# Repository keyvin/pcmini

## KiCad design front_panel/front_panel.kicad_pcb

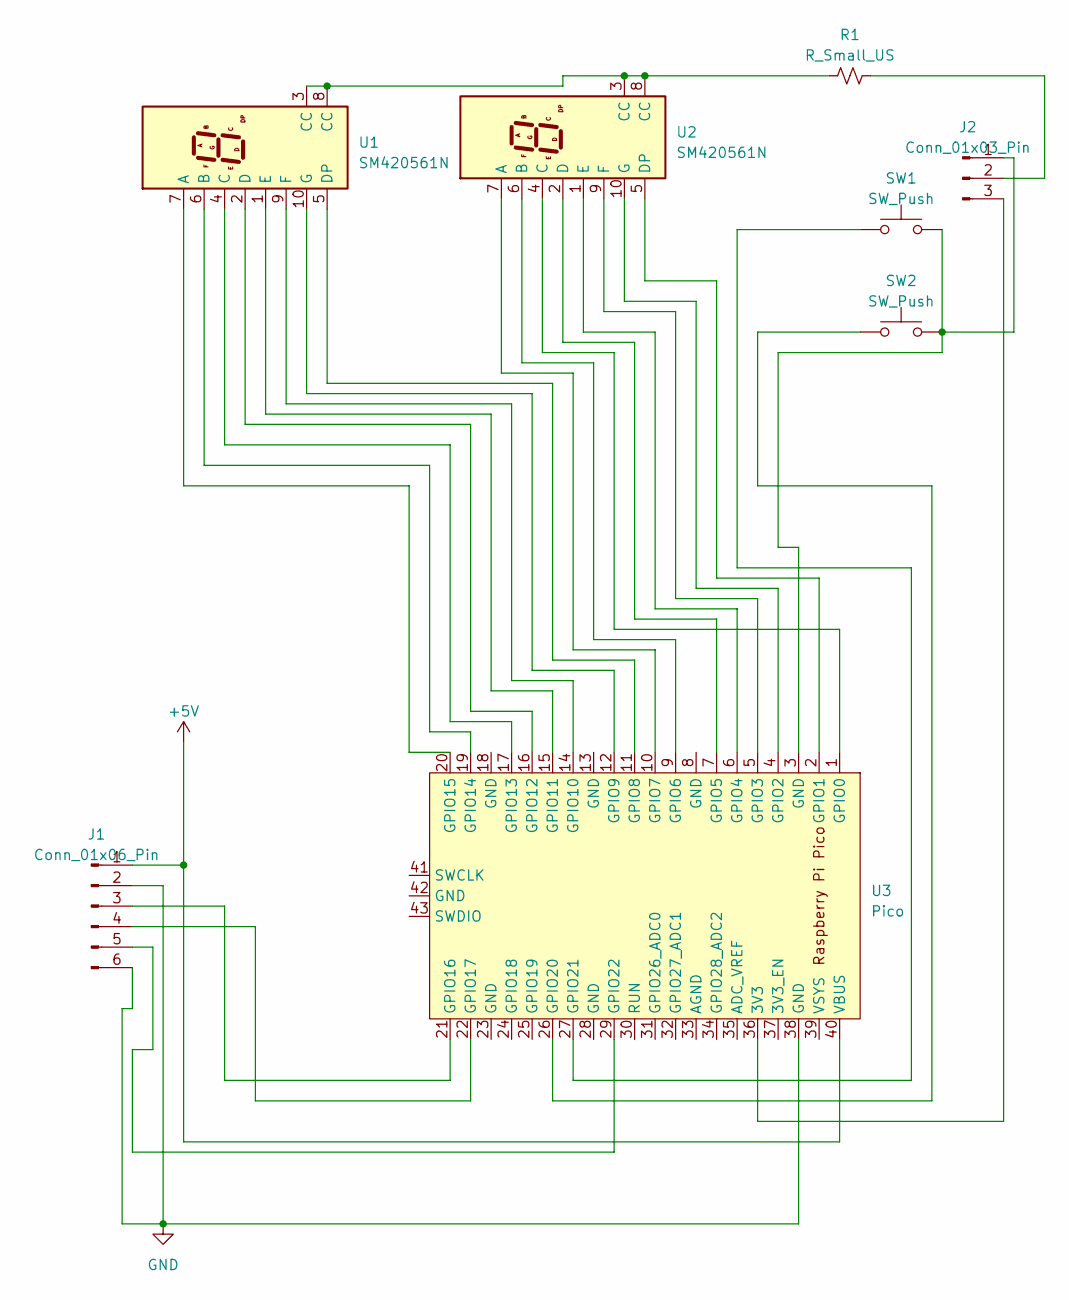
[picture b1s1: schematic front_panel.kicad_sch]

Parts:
J1: Conn_01x06_Pin; PinHeader_1x06_P2.54mm_Vertical
J2: Conn_01x03_Pin; PinHeader_1x03_P2.54mm_Vertical
R1: R_Small_US; R_Axial_DIN0207_L6.3mm_D2.5mm_P7.62mm_Horizontal
SW1, SW2: SW_Push; SW_PUSH-12mm
U1, U2: SM420561N; 7SegmentLED_LTS6760_LTS6780
U3: Pico; RPi_Pico_SMD_TH

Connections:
+5V: J1.1, U3.40 (VBUS)
GND: J1.2, J1.6, U3.38 (GND)
unnamed: J1.3, U3.21 (GPIO16)
unnamed: J1.4, U3.22 (GPIO17)
unnamed: J1.5, U3.29 (GPIO22)
unnamed: J2.1, SW1.2, SW2.2, U3.3 (GND)
unnamed: J2.2, R1.2
unnamed: J2.3, U3.36 (3V3)
unnamed: R1.1, U1.3 (CC), U1.8 (CC), U2.3 (CC), U2.8 (CC)
unnamed: U1.7 (A), U3.20 (GPIO15)
unnamed: U1.6 (B), U3.19 (GPIO14)
unnamed: U1.4 (C), U3.17 (GPIO13)
unnamed: U1.2 (D), U3.16 (GPIO12)
unnamed: U1.5 (DP), U3.11 (GPIO8)
unnamed: U1.1 (E), U3.15 (GPIO11)
unnamed: U1.9 (F), U3.14 (GPIO10)
unnamed: U1.10 (G), U3.12 (GPIO9)
unnamed: U2.7 (A), U3.10 (GPIO7)
unnamed: U2.6 (B), U3.9 (GPIO6)
unnamed: U2.4 (C), U3.1 (GPIO0)
unnamed: U2.2 (D), U3.7 (GPIO5)
unnamed: U2.5 (DP), U3.2 (GPIO1)
unnamed: U2.1 (E), U3.6 (GPIO4)
unnamed: U2.9 (F), U3.5 (GPIO3)
unnamed: U2.10 (G), U3.4 (GPIO2)
unnamed: SW2.1, U3.26 (GPIO20)
unnamed: SW1.1, U3.27 (GPIO21)

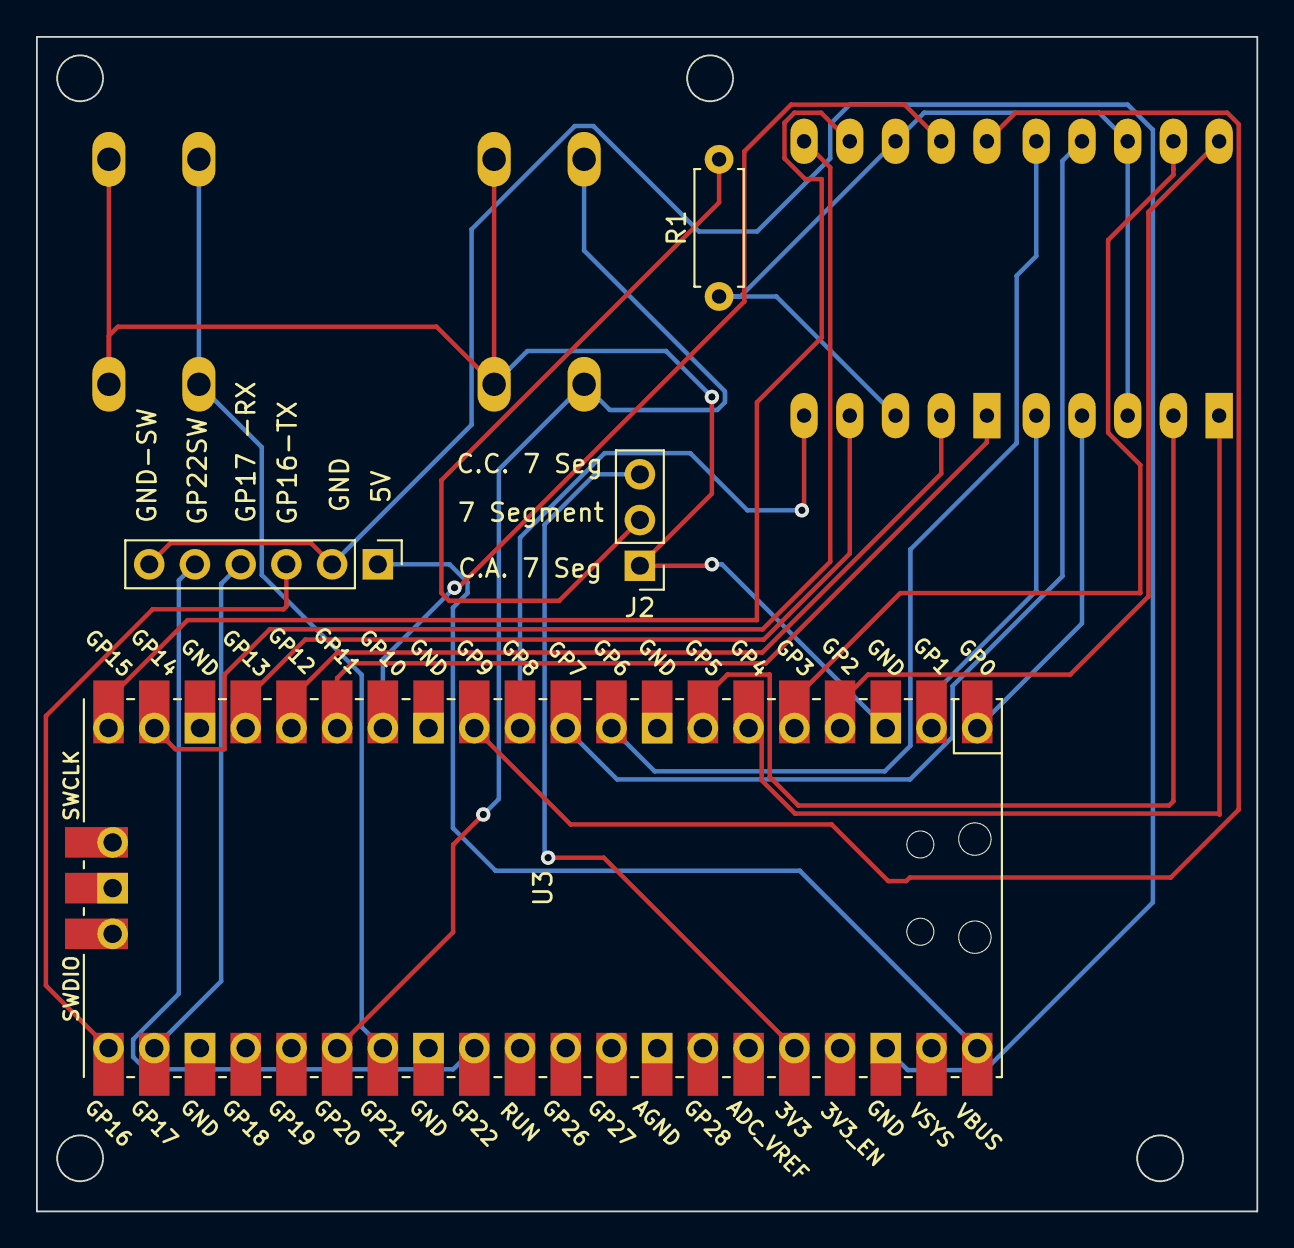
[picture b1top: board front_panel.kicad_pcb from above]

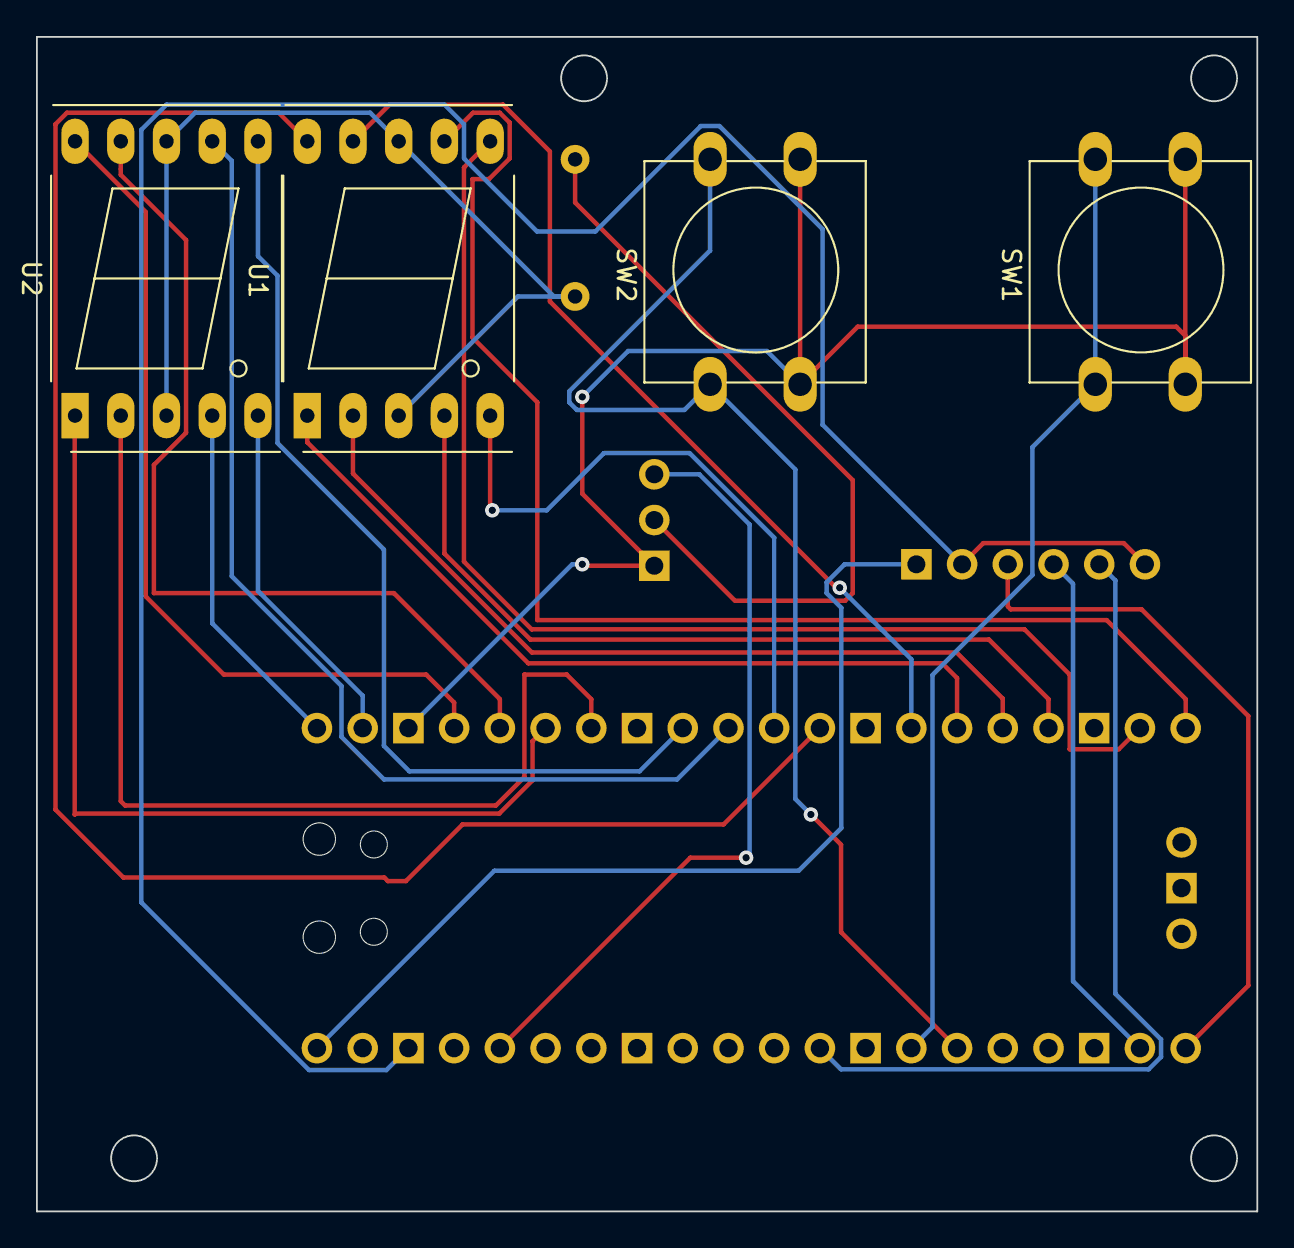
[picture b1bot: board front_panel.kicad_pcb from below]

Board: 2 copper layers, 67.8 x 65.2 mm, 8 parts (4 on the bottom side), 27 nets.

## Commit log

2025-03-02 Initial Check-in. Thicker front plate.
2025-03-08 Added kicad front panel. Probably need to import pico symbol again
2025-03-09 Front panel script working
2025-03-09 front panel and host script sketched out
2025-03-10 Added evdev template
2025-03-12 Host Script disconnects on Menu Button
2025-03-15 upgrading
2025-03-28 Was turning off the pull up resistor with second pin decleration on 20
2025-04-02 Added features to model
2025-04-03 fixed front panel bug
2025-04-03 fixed some code issues and model bolt sizes
2025-04-22 Designed front plate w/ drives
2025-04-26 front plate finished
